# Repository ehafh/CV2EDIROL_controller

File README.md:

# CV2EDIROL_controller
An open-source CV to MIDI controller for EDIROL V4 and V8 video mixers

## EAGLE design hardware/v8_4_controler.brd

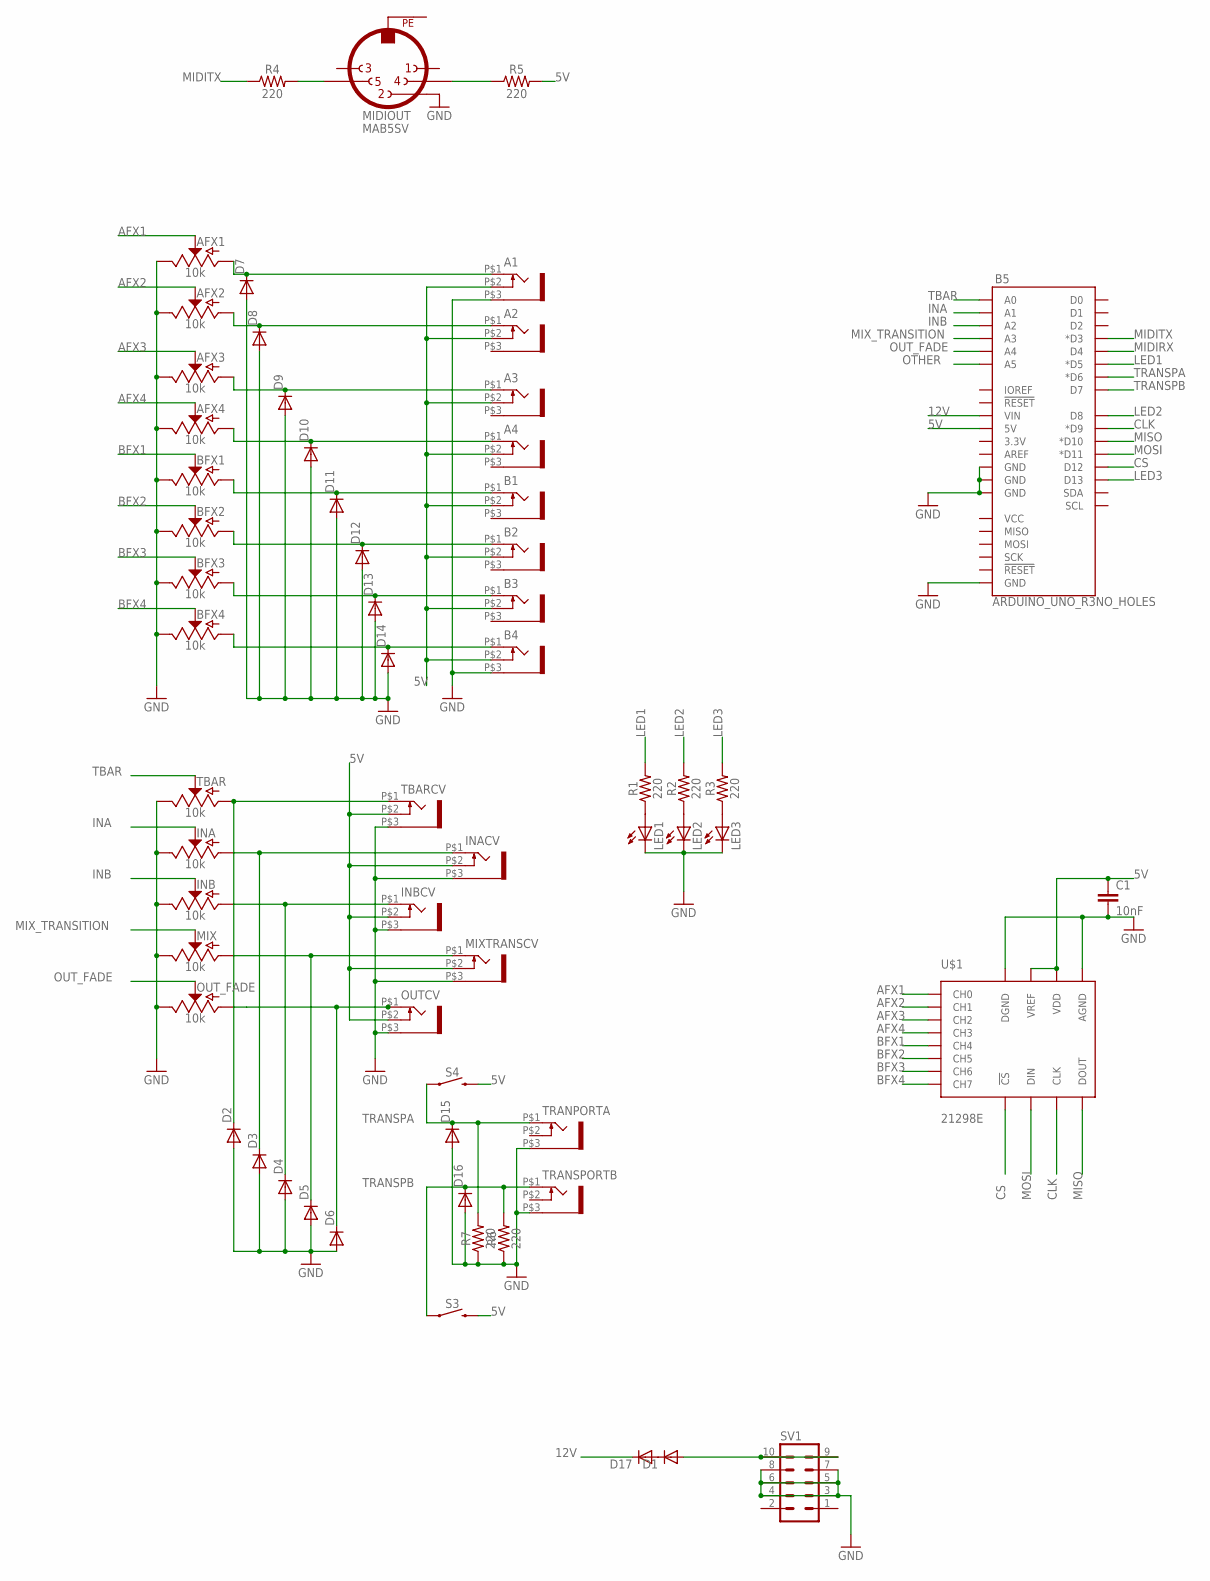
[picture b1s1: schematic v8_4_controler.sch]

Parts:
A1, A2, A3, A4: WQP-PJ301M-12_JACK
AFX1, AFX2, AFX3, AFX4: 10k; POT-PTH-ALPS
B1, B2, B3, B4: WQP-PJ301M-12_JACK
B5: ARDUINO_UNO_R3NO_HOLES; ARDUINO_R3_NO_HOLES
BFX1, BFX2, BFX3, BFX4: 10k; POT-PTH-ALPS
C1: 10nF; CAP-PTH-10MM
D1, D2, D3, D4, D5, D6, D7, D8, D9, D10, D11, D12, D13, D14, D15, D16, D17: 1N4004; DO41-10
INA: 10k; POT-PTH-ALPS
INACV: WQP-PJ301M-12_JACK
INB: 10k; POT-PTH-ALPS
INBCV: WQP-PJ301M-12_JACK
LED1, LED2, LED3: LED3MM
MIDIOUT: MAB5SV
MIX: 10k; POT-PTH-ALPS
MIXTRANSCV: WQP-PJ301M-12_JACK
OUTCV: WQP-PJ301M-12_JACK
OUT_FADE: 10k; POT-PTH-ALPS
R1, R2, R3, R4, R5, R6, R7: 220; AXIAL-0.3
S3, S4: MOMENTARY-SWITCH-SPST-PTH-6.0MM; TACTILE_SWITCH_PTH_6.0MM
SV1: MA05-2
TBAR: 10k; POT-PTH-ALPS
TBARCV: WQP-PJ301M-12_JACK
TRANPORTA: WQP-PJ301M-12_JACK
TRANSPORTB: WQP-PJ301M-12_JACK
U$1: 21298E; PDIP16

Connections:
5V: A1.P$2 (3), A2.P$2 (3), A3.P$2 (3), A4.P$2 (3), B1.P$2 (3), B2.P$2 (3), B3.P$2 (3), B4.P$2 (3), B5.5V, C1.1, INACV.P$2 (3), INBCV.P$2 (3), MIXTRANSCV.P$2 (3), OUTCV.P$2 (3), R5.P$2 (2), S3.3 (2), S4.3 (2), TBARCV.P$2 (3), U$1.P$15 (VREF), U$1.P$16 (VDD)
12V: B5.VIN, D17.C
AFX1: AFX1.P$2 (S), U$1.P$1 (CH0)
AFX2: AFX2.P$2 (S), U$1.P$2 (CH1)
AFX3: AFX3.P$2 (S), U$1.P$3 (CH2)
AFX4: AFX4.P$2 (S), U$1.P$4 (CH3)
BFX1: BFX1.P$2 (S), U$1.P$5 (CH4)
BFX2: BFX2.P$2 (S), U$1.P$6 (CH5)
BFX3: BFX3.P$2 (S), U$1.P$7 (CH6)
BFX4: BFX4.P$2 (S), U$1.P$8 (CH7)
CLK: B5.D9 (*D9), U$1.P$13 (CLK)
CS: B5.D12, U$1.P$10 (!CS)
GND: A1.P$3 (1), AFX1.P$1 (E), AFX2.P$1 (E), AFX3.P$1 (E), AFX4.P$1 (E), B4.P$3 (1), B5.GND@1 (GND), B5.GND@2 (GND), B5.GND@3 (GND), B5.GND@4 (GND), BFX1.P$1 (E), BFX2.P$1 (E), BFX3.P$1 (E), BFX4.P$1 (E), C1.2, D2.A, D3.A, D4.A, D5.A, D6.A, D7.A, D8.A, D9.A, D10.A, D11.A, D12.A, D13.A, D14.A, D15.A, D16.A, INA.P$1 (E), INACV.P$3 (1), INB.P$1 (E), INBCV.P$3 (1), LED1.K (C), LED2.K (C), LED3.K (C), MIDIOUT.2, MIX.P$1 (E), MIXTRANSCV.P$3 (1), OUTCV.P$3 (1), OUT_FADE.P$1 (E), R6.P$1 (1), R7.P$1 (1), SV1.3, SV1.4, SV1.5, SV1.6, SV1.7, SV1.8, TBAR.P$1 (E), TBARCV.P$3 (1), TRANPORTA.P$3 (1), TRANSPORTB.P$3 (1), U$1.P$9 (DGND), U$1.P$14 (AGND)
INA: B5.A1, INA.P$2 (S)
INB: B5.A2, INB.P$2 (S)
LED1: B5.D5 (*D5), R1.P$2 (2)
LED2: B5.D8, R2.P$2 (2)
LED3: B5.D13, R3.P$2 (2)
MIDIRX: B5.D4
MIDITX: B5.D3 (*D3), R4.P$1 (1)
MISO: B5.D10 (*D10), U$1.P$12 (DOUT)
MIX_TRANSITION: B5.A3, MIX.P$2 (S)
MOSI: B5.D11 (*D11), U$1.P$11 (DIN)
unnamed: A1.P$1 (2), AFX1.P$3 (A), D7.C
unnamed: A2.P$1 (2), AFX2.P$3 (A), D8.C
unnamed: A3.P$1 (2), AFX3.P$3 (A), D9.C
unnamed: A4.P$1 (2), AFX4.P$3 (A), D10.C
unnamed: B1.P$1 (2), BFX1.P$3 (A), D11.C
unnamed: B2.P$1 (2), BFX2.P$3 (A), D12.C
unnamed: B3.P$1 (2), BFX3.P$3 (A), D13.C
unnamed: B4.P$1 (2), BFX4.P$3 (A), D14.C
unnamed: MIDIOUT.4, R5.P$1 (1)
unnamed: LED1.A, R1.P$1 (1)
unnamed: MIDIOUT.5, R4.P$2 (2)
unnamed: LED2.A, R2.P$1 (1)
unnamed: LED3.A, R3.P$1 (1)
unnamed: D2.C, TBAR.P$3 (A), TBARCV.P$1 (2)
unnamed: D3.C, INA.P$3 (A), INACV.P$1 (2)
unnamed: D4.C, INB.P$3 (A), INBCV.P$1 (2)
unnamed: D5.C, MIX.P$3 (A), MIXTRANSCV.P$1 (2)
unnamed: D6.C, OUTCV.P$1 (2), OUT_FADE.P$3 (A)
unnamed: D1.A, SV1.9, SV1.10
unnamed: D1.C, D17.A
OTHER: B5.A5
OUT_FADE: B5.A4, OUT_FADE.P$2 (S)
PE: MIDIOUT.PE
TBAR: B5.A0, TBAR.P$2 (S)
TRANSPA: B5.D6 (*D6), D15.C, R7.P$2 (2), S4.1, TRANPORTA.P$1 (2)
TRANSPB: B5.D7, D16.C, R6.P$2 (2), S3.1, TRANSPORTB.P$1 (2)

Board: 2 copper layers, 62 parts (1 on the bottom side), 46 nets, no tracks yet.

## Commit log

2021-08-26 Add files via upload
    firmware for controller and program to test the knobs and buttons of the controller
2021-08-27 Add files via upload
    hardware files WIP

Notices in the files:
parts and their libraries:
SparkFun-Resistors: Licensing: Creative Commons ShareAlike 4.0 International - https://creativecommons.org/licenses/by-sa/4.0
